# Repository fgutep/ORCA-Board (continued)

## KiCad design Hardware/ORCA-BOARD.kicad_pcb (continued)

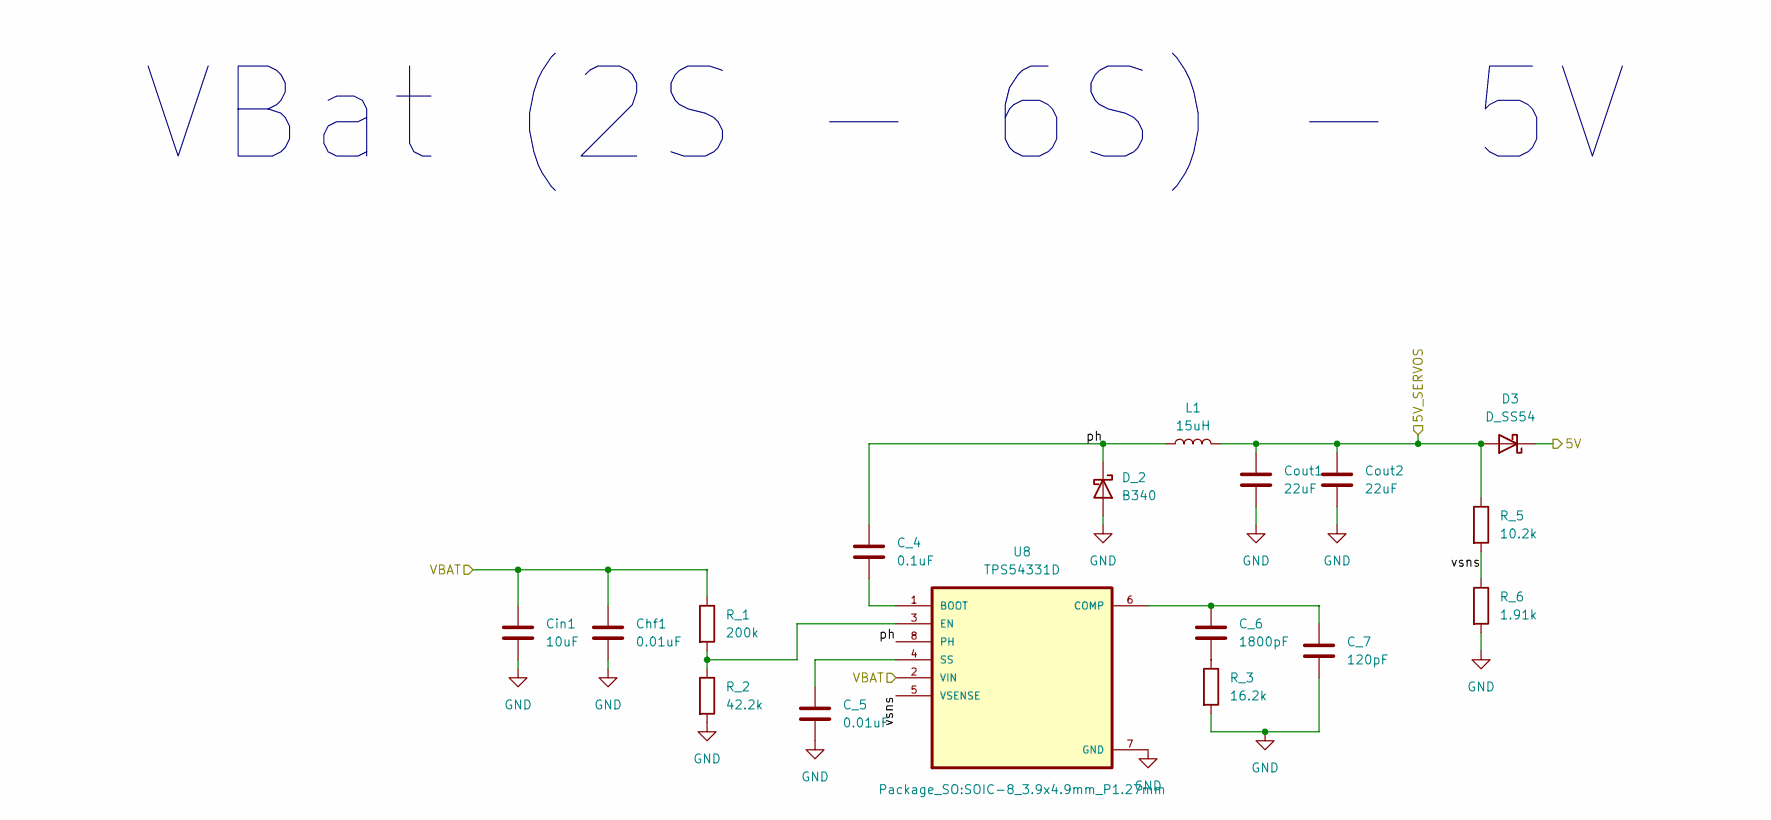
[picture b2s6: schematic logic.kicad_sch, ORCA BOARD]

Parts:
C_4: 0.1uF; C_0603_1608Metric_Pad1.08x0.95mm_HandSolder
C_5: 0.01uF; C_0603_1608Metric_Pad1.08x0.95mm_HandSolder
C_6: 1800pF; C_0603_1608Metric_Pad1.08x0.95mm_HandSolder
C_7: 120pF; C_0603_1608Metric_Pad1.08x0.95mm_HandSolder
Chf1: 0.01uF; C_0603_1608Metric_Pad1.08x0.95mm_HandSolder
Cin1: 10uF; C_1206_3216Metric_Pad1.33x1.80mm_HandSolder
Cout1, Cout2: 22uF; C_1206_3216Metric_Pad1.33x1.80mm_HandSolder
D3: D_SS54; D_SMA_Handsoldering
D_2: B340; D_SMC
L1: 15uH; L_7.3x7.3_H3.5
R_1: 200k; R_0603_1608Metric_Pad0.98x0.95mm_HandSolder
R_2: 42.2k; R_0603_1608Metric_Pad0.98x0.95mm_HandSolder
R_3: 16.2k; R_0603_1608Metric_Pad0.98x0.95mm_HandSolder
R_5: 10.2k; R_0603_1608Metric_Pad0.98x0.95mm_HandSolder
R_6: 1.91k; R_0603_1608Metric_Pad0.98x0.95mm_HandSolder
U8: TPS54331D; SOIC-8_3.9x4.9mm_P1.27mm

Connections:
/2s-6s_to_5v/ph: C_4.1, D_2.1 (K), L1.1, U8.8 (PH)
/2s-6s_to_5v/vsns: R_5.2, R_6.1, U8.5 (VSENSE)
/5V: D3.1 (K); also elsewhere on the board
/5V_SERVOS: Cout1.1, Cout2.1, D3.2 (A), L1.2, R_5.1; also elsewhere on the board
GND: C_5.2, C_7.2, Chf1.2, Cin1.2, Cout1.2, Cout2.2, D_2.2 (A), R_2.2, R_3.2, R_6.2, U8.7 (GND); also elsewhere on the board
unnamed: C_6.2, R_3.1
unnamed: C_4.2, U8.1 (BOOT)
unnamed: C_6.1, C_7.1, U8.6 (COMP)
unnamed: R_1.2, R_2.1, U8.3 (EN)
unnamed: C_5.1, U8.4 (SS)
VBUS: Chf1.1, Cin1.1, R_1.1, U8.2 (VIN); also elsewhere on the board

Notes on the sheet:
VBat (2S - 6S) - 5V

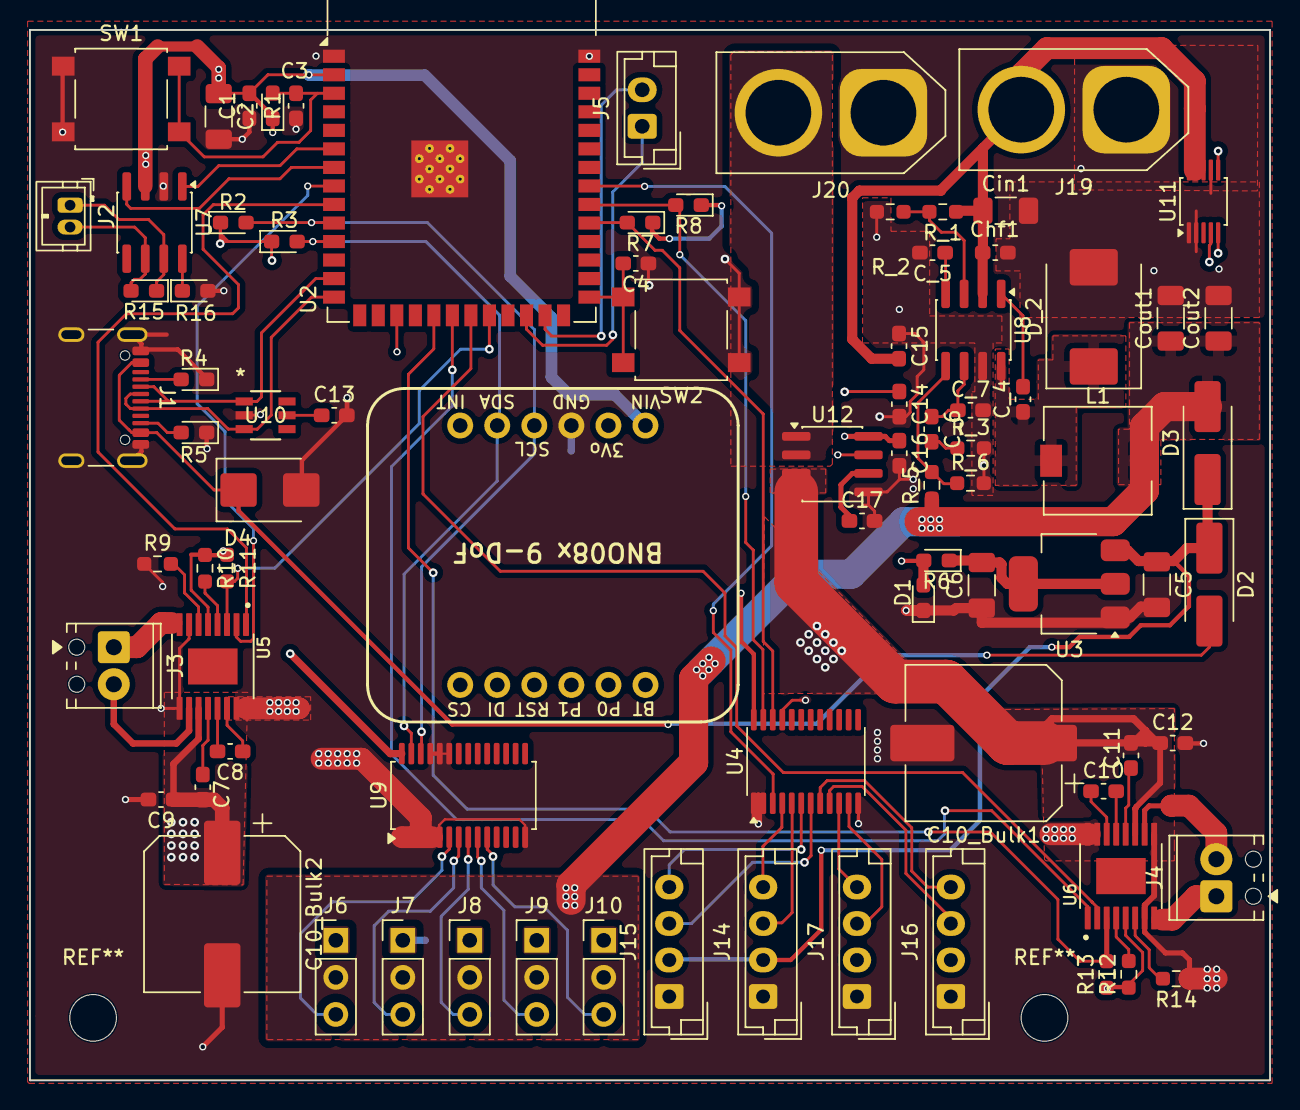
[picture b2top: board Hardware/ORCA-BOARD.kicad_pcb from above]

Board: 4 copper layers, 85.0 x 72.0 mm, 84 parts (0 on the bottom side), 70 nets.

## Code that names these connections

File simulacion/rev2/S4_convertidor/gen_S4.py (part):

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
BASE = r"""@TITLE@
* Base: S4a.cir (LM5175 + Q1-Q4 BUK9Y3R5-40E + L + caps). Agregados Rev2: entrada Q5 + salida Q6/Q7 + bleeder. ISNS (N010 N010) igual que S4a.
XU1 N002 N004 VIN N005 N006 N008 SLOPE SS COMP 0 FB VOUT N010 N010 CSG CS PGOOD SW2 HDRV2 N007 LDRV2 0 VCC VOUT LDRV1 N009 HDRV1 SW1 NC_02 LM5175_TRANS SS_1=0
R1 N008 0 71.5k
C1 SLOPE 0 270p
C2 SS 0 {CSS}
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.include ..\modelos\BUK9Y3R5-40E.lib
.include ..\modelos\SiRS4401DP_PS.TXT
.include "..\modelos\2n7002k_ps Rev B.lib"
.ic V(ss)=0 V(comp)=0 V(vout)=0
.param CSS=12n
.param VIN_dc=@VIN@
.param VOUT_target=@VOUT@
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.meas TRAN fb_reg_c AVG V(fb) FROM 2.8m TO 3.0m
.meas TRAN vyl_max_reg MAX V(vyl) FROM 2.4m TO 2.6m
.meas TRAN t_pgood WHEN V(pgood)=3.5 RISE=1
.meas TRAN t_vout11 WHEN V(vout)=11 RISE=1
.meas TRAN vss_end FIND V(ss) AT 3.0m
.meas TRAN vcomp_end FIND V(comp) AT 3.0m
.meas TRAN vgs5_reg AVG V(g5)-V(vin) FROM 2.4m TO 2.6m
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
